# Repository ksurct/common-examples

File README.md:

# common-examples
A repo filled with common examples used throughout our team

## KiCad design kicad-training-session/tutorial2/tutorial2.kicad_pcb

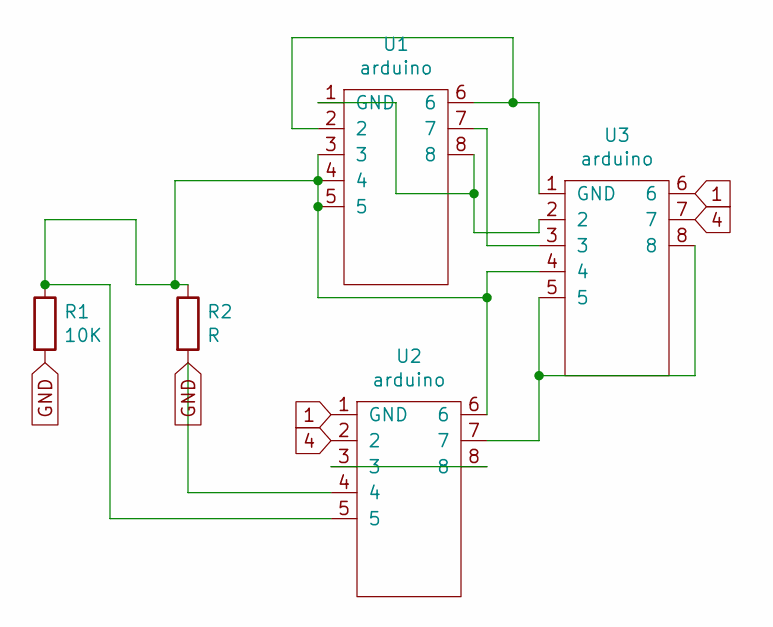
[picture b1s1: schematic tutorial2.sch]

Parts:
R1: 10K; R_Axial_DIN0207_L6.3mm_D2.5mm_P10.16mm_Horizontal
R2: R; R_Axial_DIN0207_L6.3mm_D2.5mm_P10.16mm_Horizontal
U1, U2, U3: arduino

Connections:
1: U2.1 (GND), U3.6
4: U2.2, U3.7
GND: R1.2, R2.2, U2.4
unnamed: R1.1, R2.1, U1.3, U1.4, U1.5, U2.5, U2.6, U3.4
unnamed: U1.1 (GND), U1.8, U3.2
unnamed: U1.2, U1.6, U3.1 (GND)
unnamed: U1.7, U3.3
unnamed: U2.3, U2.8
unnamed: U2.7, U3.5, U3.8

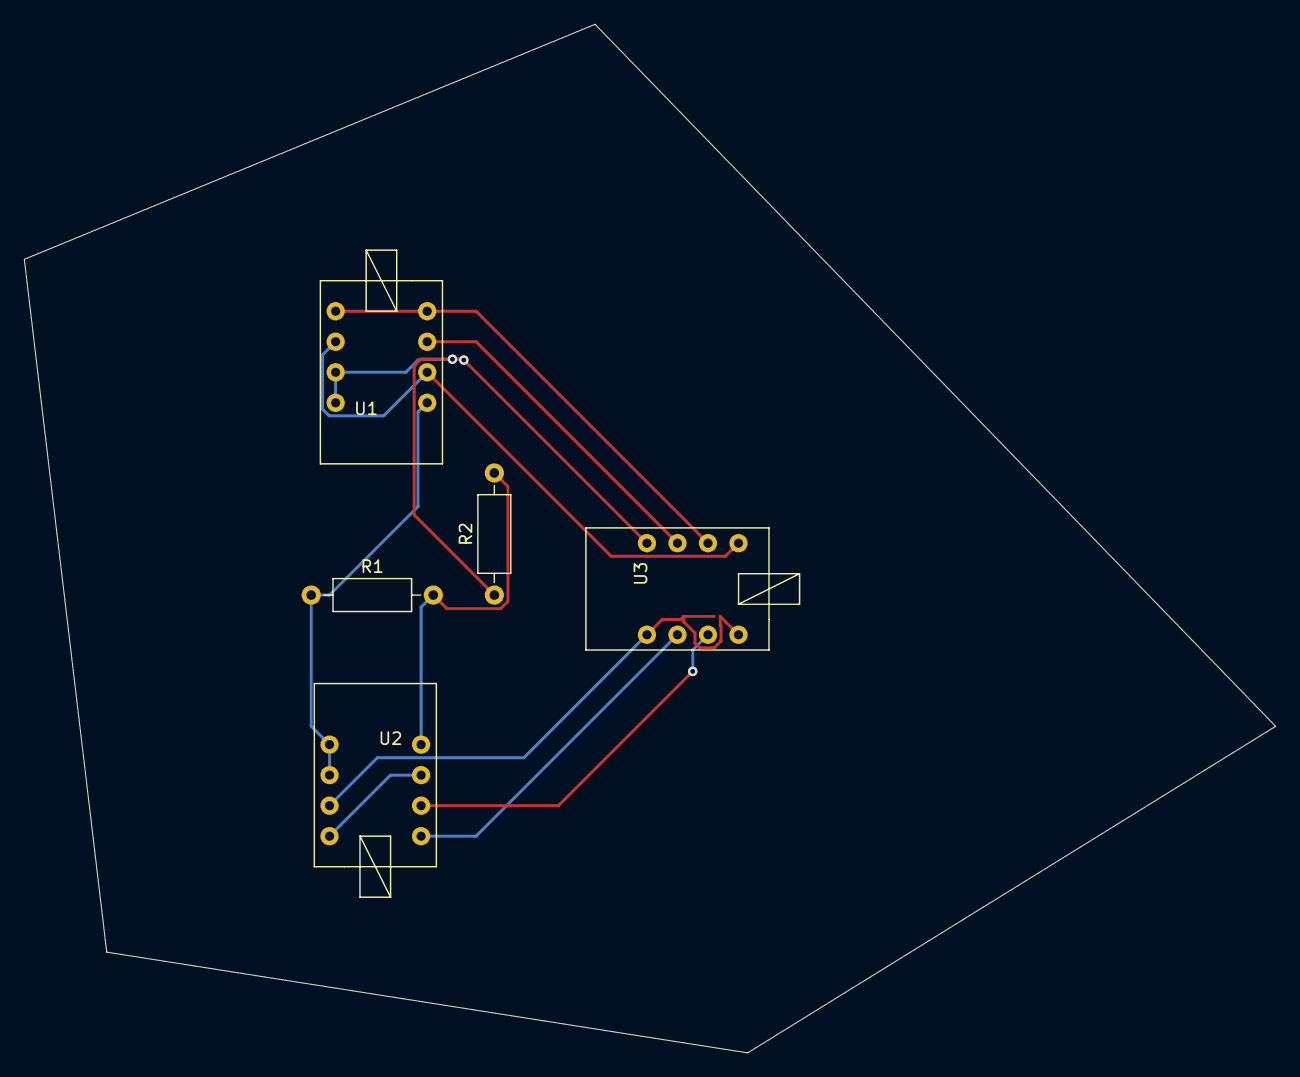
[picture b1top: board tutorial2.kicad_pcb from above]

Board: 2 copper layers, 104.1 x 85.6 mm, 5 parts (0 on the bottom side), 9 nets.

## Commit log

2021-10-19 Got teensy and rpi (untested) example up
2021-10-19 Fixed
2021-10-20 Added sensor code
2021-10-24 Added gps and kicad examples
2021-10-28 Magsensor Example
2021-12-29 Started making a generic robot
2021-12-30 Added more solid works
2021-12-31 Added course creation
2021-12-31 Integrated course with robot sim
2021-12-31 started ray casting
2022-01-02 Got ray casting working
2022-01-03 More
2022-01-04 Pretty much done, just need to package up nicely
2022-01-04 Cleaned and provided docs
2022-01-04 Cleaned up and got ignores in
2022-01-04 Made to work on windows
2022-01-20 Clean
2022-01-26 Added RobotDriving.py
2022-02-03 some documentation added
2022-02-03 Added distance limit for camera
2022-03-28 Added many things, including error and starting angle
2022-03-28 Small changes
2022-03-29 Added color maping to the camera
2022-03-30 Added arc movement
2022-03-30 Fixed constant move
2022-03-31 No tkinter
2022-03-31 Added px conversions
2022-03-31 Added calls to unkown methods
2022-03-31 Added debug prints
2022-03-31 Debug print
2022-04-01 Not done with relative coords
2022-04-02 Done with relative coords
2022-04-05 Made sensor cone angle
